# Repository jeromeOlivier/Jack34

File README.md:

# Jack34 Keyboard

Preliminary design of an ortholinear 34 key keyboard layout with Nice!Nano compatibility.

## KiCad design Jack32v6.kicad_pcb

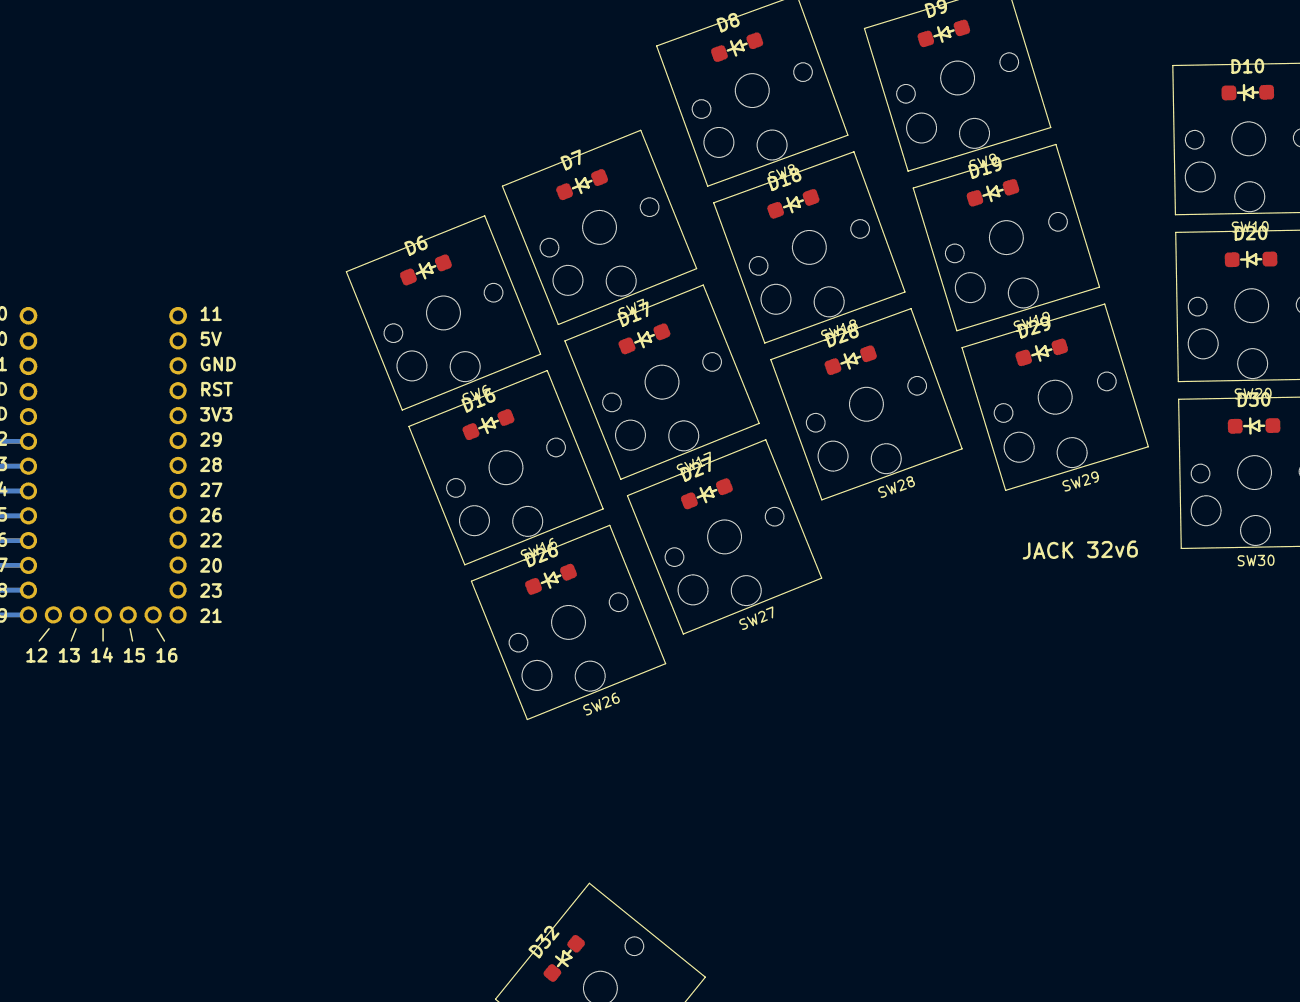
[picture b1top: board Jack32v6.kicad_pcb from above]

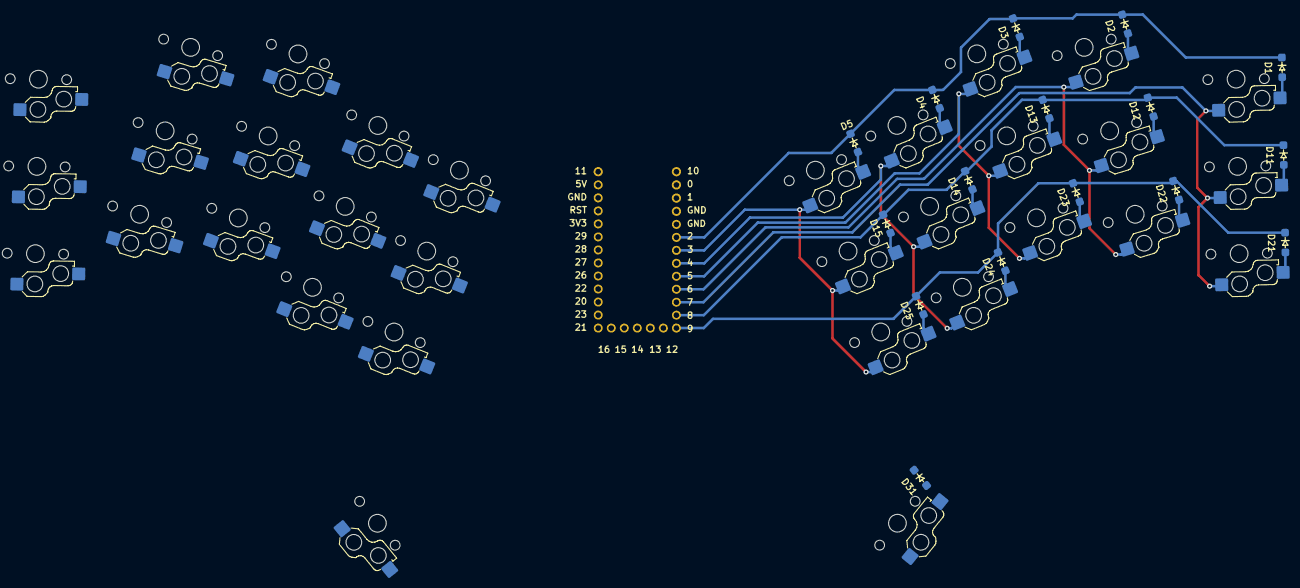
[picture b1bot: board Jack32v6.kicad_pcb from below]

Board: 2 copper layers, 65 parts (16 on the bottom side), 50 nets.

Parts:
D1, D2, D3, D4, D5, D6, D7, D8, D9, D10, D11, D12, D13, D14, D15, D16, D17, D18, D19, D20, D21, D22, D23, D24, D25, D26, D27, D28, D29, D30, D31, D32: D_Small; D_SOD-123
SW1, SW2, SW3, SW4, SW6, SW7, SW8, SW9, SW10, SW11, SW12, SW13, SW14, SW16, SW17, SW18, SW19, SW20, SW21, SW22, SW23, SW24, SW26, SW27, SW28, SW29, SW30, SW31, SW32: MX_SW_HS; Hotswap_Choc_V1_1.00u
U1: eliteC; my_microcontroller
locked: MX_SW_HS; Hotswap_Choc_V1_1.00u
locked#2, locked#3: MX_SW_HS; Hotswap_Choc_V1_1.00u

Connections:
C0: SW1.1, SW11.1, SW21.1, U1.7
C1: SW2.1, SW12.1, SW22.1, U1.6
C2: SW3.1, SW13.1, SW23.1, U1.5
C3: SW4.1, SW14.1, SW24.1, U1.4
C4: SW31.1, U1.3, locked.1, locked#2.1, locked#3.1
C5: SW6.1, SW16.1, SW26.1, SW32.1, U1.28
C6: SW7.1, SW17.1, SW27.1, U1.27
C7: SW8.1, SW18.1, SW28.1, U1.26
C8: SW9.1, SW19.1, SW29.1, U1.22
C9: SW10.1, SW20.1, SW30.1, U1.20
unnamed: D1.2 (A), SW1.2
unnamed: D2.2 (A), SW2.2
unnamed: D3.2 (A), SW3.2
unnamed: D4.2 (A), SW4.2
unnamed: D5.2 (A), locked#2.2
unnamed: D6.2 (A), SW6.2
unnamed: D7.2 (A), SW7.2
unnamed: D8.2 (A), SW8.2
unnamed: D9.2 (A), SW9.2
unnamed: D10.2 (A), SW10.2
unnamed: D11.2 (A), SW11.2
unnamed: D12.2 (A), SW12.2
unnamed: D13.2 (A), SW13.2
unnamed: D14.2 (A), SW14.2
unnamed: D15.2 (A), locked#3.2
unnamed: D16.2 (A), SW16.2
unnamed: D17.2 (A), SW17.2
unnamed: D18.2 (A), SW18.2
unnamed: D19.2 (A), SW19.2
unnamed: D20.2 (A), SW20.2
unnamed: D21.2 (A), SW21.2
unnamed: D22.2 (A), SW22.2
unnamed: D23.2 (A), SW23.2
unnamed: D24.2 (A), SW24.2
unnamed: D25.2 (A), locked.2
unnamed: D26.2 (A), SW26.2
unnamed: D27.2 (A), SW27.2
unnamed: D28.2 (A), SW28.2
unnamed: D29.2 (A), SW29.2
unnamed: D30.2 (A), SW30.2
unnamed: D31.2 (A), SW31.2
unnamed: D32.2 (A), SW32.2
R0: D1.1 (K), D2.1 (K), D3.1 (K), D4.1 (K), D5.1 (K), U1.2
R1: D11.1 (K), D12.1 (K), D13.1 (K), D14.1 (K), D15.1 (K), U1.8
R2: D21.1 (K), D22.1 (K), D23.1 (K), D24.1 (K), D25.1 (K), U1.9
R3: D31.1 (K), U1.12
R4: D6.1 (K), D7.1 (K), D8.1 (K), D9.1 (K), D10.1 (K), U1.29
R5: D16.1 (K), D17.1 (K), D18.1 (K), D19.1 (K), D20.1 (K), U1.23
R6: D26.1 (K), D27.1 (K), D28.1 (K), D29.1 (K), D30.1 (K), U1.21
R7: D32.1 (K), U1.16

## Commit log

2023-08-30 added README
2024-05-29 hotswap start
